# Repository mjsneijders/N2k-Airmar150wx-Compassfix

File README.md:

# N2k-Airmar150wx-Compassfix

filter and substiture crappy output from Airmar 150Wx

using arduino due,  and both it's can controllers

-substitute wmm2020 variation

-filter out uncompensated compass heading

-filter out truewind direction (its calculated using uncompensated compass)

-add proper truewind direction calculated from other compass, and wmm2020 variation

-add truewind angle... (airmar didnt even supply it in the first place

-passthrough everything else coming from the airmar

N2k needed libraries:

https://github.com/ttlappalainen/NMEA2000

https://github.com/ttlappalainen/NMEA2000_due

https://github.com/ttlappalainen/CAN_BUS_Shield

WMM 2020 library

https://github.com/miniwinwm/WMM_Tiny

Due Flash storage libray

https://github.com/sebnil/DueFlashStorage

Time library

https://github.com/PaulStoffregen/Time

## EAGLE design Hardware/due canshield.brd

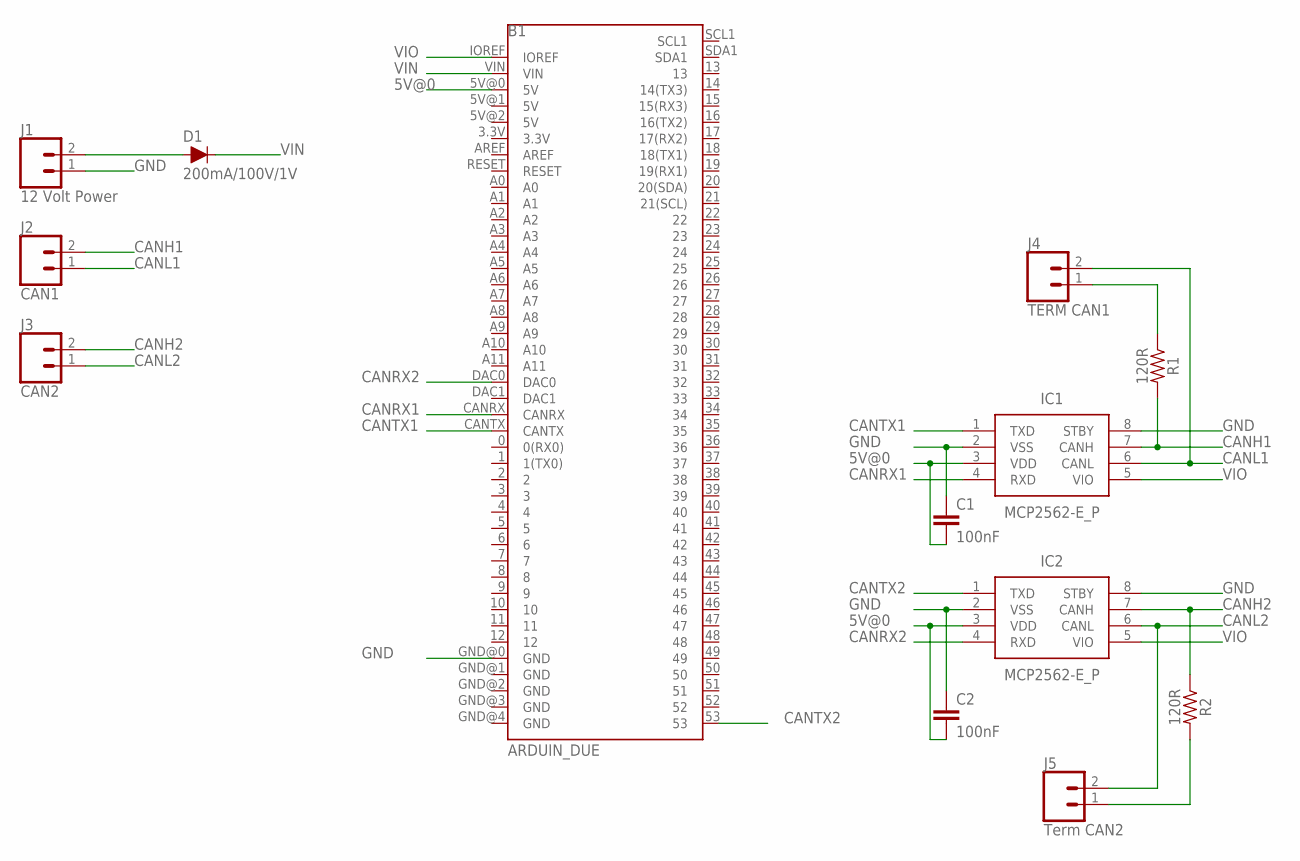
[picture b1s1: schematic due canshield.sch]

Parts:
B1: ARDUIN_DUE; ARDUINODUE
C1, C2: 100nF; CAP-PTH-10MM
D1: 200mA/100V/1V; DIODE-1N4148
IC1, IC2: MCP2562-E_P; DIP781W56P254L950H533Q8N
J1: 12 Volt Power; SCREWTERMINAL-3.5MM-2
J2: CAN1; SCREWTERMINAL-3.5MM-2
J3: CAN2; SCREWTERMINAL-3.5MM-2
J4: TERM CAN1; 1X02_LOCK_LONGPADS
J5: Term CAN2; 1X02_LOCK_LONGPADS
R1, R2: 120R; AXIAL-0.3

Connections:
5V@0: B1.5V@0 (5V), C1.2, C2.2, IC1.3 (VDD), IC2.3 (VDD)
CANH1: IC1.7 (CANH), J2.2, R1.P$2 (2)
CANH2: IC2.7 (CANH), J3.2, R2.P$1 (1)
CANL1: IC1.6 (CANL), J2.1, J4.2
CANL2: IC2.6 (CANL), J3.1, J5.2
CANRX1: B1.CANRX, IC1.4 (RXD)
CANRX2: B1.DAC0, IC2.4 (RXD)
CANTX1: B1.CANTX, IC1.1 (TXD)
CANTX2: B1.53, IC2.1 (TXD)
GND: B1.GND@0 (GND), C1.1, C2.1, IC1.2 (VSS), IC1.8 (STBY), IC2.2 (VSS), IC2.8 (STBY), J1.1
unnamed: D1.A, J1.2
unnamed: J5.1, R2.P$2 (2)
unnamed: J4.1, R1.P$1 (1)
VIN: B1.VIN, D1.C
VIO: B1.IOREF, IC1.5 (VIO), IC2.5 (VIO)

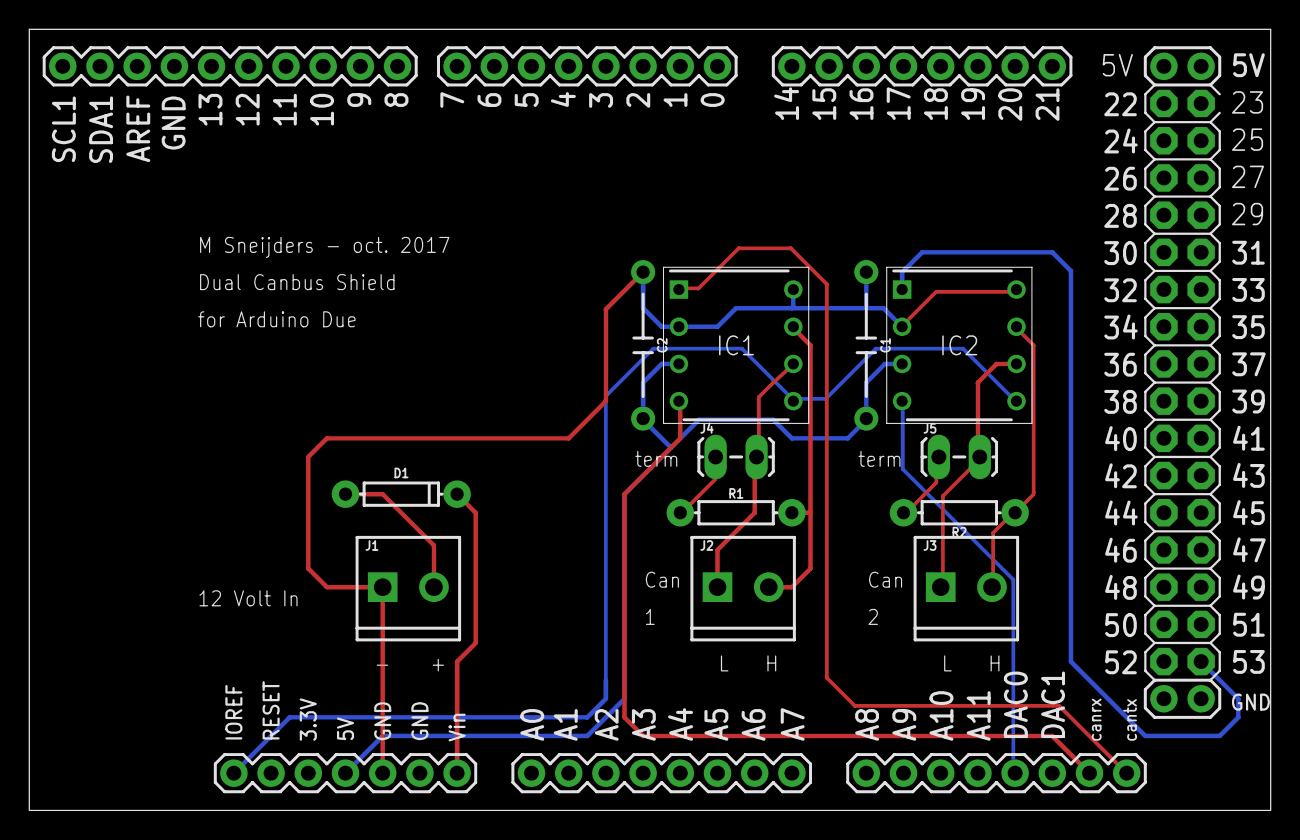
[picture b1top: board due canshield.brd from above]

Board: 2 copper layers, 84.8 x 53.3 mm, 13 parts (0 on the bottom side), 15 nets.

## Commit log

2022-03-11 add hardware
2022-03-11 update applicable PGN's
2022-03-11 typos
    compile first, commit later
2022-03-12 Add Watchdog reset, and activity blink led
2022-03-14 remove unneeded product and device information from inner canbus setup

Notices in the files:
parts and their libraries:
SparkFun-Capacitors: Licensing: Creative Commons ShareAlike 4.0 International - https://creativecommons.org/licenses/by-sa/4.0
